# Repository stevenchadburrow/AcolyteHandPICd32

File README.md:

<b><h1>Acolyte Hand PIC'd 32 Retraux Computer and Video Game Console</h1></b>

<b>Background</b>

Why build a "computer"?  Why build a "video game console"?  

I had been programming video games for about 20 years before all of this.  It started in high school on Borland Turbo C++ in the computer lab, and then in college on a Ubuntu Linux computer with g++ and OpenGL.  Most of my early attempts are not even worth mentioning though I tried different genres such as FPS and RTS.  After graduate school and getting a job at the local college as a math teacher, I began trying to make a non-violent video game, namely a <a href="https://en.wikipedia.org/wiki/Harvest_Moon_(video_game)">Harvest Moon</a> clone.  It seems that <a href="https://en.wikipedia.org/wiki/Stardew_Valley">Stardew Valley</a> beat me to it!  After many attempts on many different platforms, including Linux/OpenGL/C++, HTML/Javascript, and Android/Java, I have declared them all as 'demos', though I learned a lot from that time.  Meanwhile, I began programming 'arcade' video games for our annual Math Appreciation Day events, to have on display and allow students to play during the event.  A few are listed <a href="https://github.com/stevenchadburrow/MathDayGames">here</a>.  

In Fall 2021, after starting research on a water-based calculator, I thought to myself, "Wouldn't electricity be so much easier?"  After stumbling upon <a href="https://wilsonminesco.com/">Garth Wilson's 6502 Primer</a>, I emailed him and he invited me to join the <a href="http://forum.6502.org/">6502.org Forum</a>.  I began researching and prototyping (aka breadboarding) with basic logic chips, and learning how to create schematics.  While learning more about digital electronics, I found The 8-Bit Guy, Adrian's Digital Basement, and Ben Eater on Youtube.

Inspired by The 8-Bit Guy's <a href="https://www.youtube.com/watch?v=ayh0qebfD2g">"Dream Computer"</a>, and after many initial attempts (aka failures) and a couple of awesome successes, I eventually produced the original <a href="https://github.com/stevenchadburrow/AcolyteComputer">Acolyte Computer</a> using a W65C02 processor.  I had great help from Garth Wilson and the guys on the 6502.org Forum as I worked through many prototypes to get to that point.  I was able to display this and other projects at the Math Appreciation Day events playing video games such as Space Invaders, Tetris, and Rogue.

From there, the project grew to the <a href="https://github.com/stevenchadburrow/NewAcolyte">New Acolyte</a> coupled with an XC9572XL CPLD, then the <a href="https://github.com/stevenchadburrow/Acolyte816">Acolyte '816</a> using a W65C816 processor coupled with a PIC16F886 microcontroller as a bootloader.  Wanting to continue pursuing PIC microcontrollers, I created the original <a href="https://github.com/stevenchadburrow/AcolyteHandPICd">Acolyte Hand PIC'd</a> using the PIC18F47J13 microcontroller, then the <a href="https://github.com/stevenchadburrow/AcolyteHandPICd24">Acolyte Hand PIC'd 24</a> using the PIC24EP512GP204 microcontroller finally without a coupled CPLD.  During Summer 2024, I programmed a 2-player <a href="https://www.youtube.com/watch?v=8EHRpKk9gPc">Pokemon demo</a> using <a href="https://tuxemon.org/">Tuxemon</a> art assets, pushing that PIC24 to the limit.

This project, the Acolyte Hand PIC'd 32, is supposed to show the culmination of my knowledge in PCB design and microcontroller programming over the past 3 years.  The intention is to create a standardized development platform for many new video games that will be displayed during the Math Appreciation Day events.

<b>Microcontroller</b>

PIC32MZ2048EFH144 running at 200 MHz
<br>
Internal memory of 512KB of RAM and 2MB of Flash ROM

<b>Video</b>

VGA 800x600 max resolution (720x512 typical resolution) at 72 Hz with 256 colors or 65K colors

<b>Audio</b>

Dual 8-bit audio channels

<b>HID</b>

2x Sega Genesis controller ports
<br>
Dual PS/2 port for keyboard and mouse through splitter
<br>
USB port for keyboard, mouse, or Xbox-360 controller

<b>File System</b>

Elm-Chan's <a href="http://elm-chan.org/fsw/ff/">FatFS Generic FAT Filesystem Module</a> using SPI Micro SD Card adapter
<br>
(use command 'sudo mkfs.vfat /dev/sdX' to format SDcard)

<b>UART</b>

FT232RL USB-to-UART adapter
<br>
(use command 'sudo picocom /dev/ttyUSB0' for default 9600 baud connection)

<b>Custom Applications</b>

Tetra - Tetris clone recopied from my previous PIC-related projects
<br>
Scratchpad - Proof-of-concept 'text editor' without save/load features
<br>
AV Demo - Audio/Video playback of modified video files with a resolution 240x192 at 15 FPS with 65K colors and dual 8-bit audio

<b>Gameboy Emulator</b>

Mahyar Koshkouei's <a href="https://github.com/deltabeard/Peanut-GB">Peanut-GB (with MiniGB-APU) Gameboy Emulator</a>
<br>
Added support for GBC default color palettes, custom palettes, game file save/load, and screen size and refresh rate adjustments
<br>
Tested with many games, including: Tetris, Dr. Mario, Balloon Kid, Zelda: Link's Awakening, Tobu Tobu Girl, Pokemon Red, and Pokemon Kanto Expansion Pak

<b>Links</b>

<a href="https://www.aidanmocke.com/">https://www.aidanmocke.com/</a> for a bunch of PIC32MZ projects (without Harmony), including USB.<br>
<a href="http://elm-chan.org/">http://elm-chan.org/</a> for a bunch of projects, including MMC (aka SDcard) and FatFs.<br>
<a href="https://github.com/deltabeard/">https://github.com/deltabeard/</a> for a bunch of projects, including Peanut-GB and MiniGB-APU projects.<br>
<a href="https://hackaday.com/2025/01/13/homebrew-retro-console-runs-on-pic32/">https://hackaday.com/2025/01/13/homebrew-retro-console-runs-on-pic32/</a> for the Hack-A-Day article!<br>

<b>Look Ma, no bodges! (showing Version 2 board)</b>
<br>

<b>3D printed case fits perfectly! (showing Version 1 board)</b>
<br>

<b>Main menu format with splash screen.</b>
<br>

<b>Gotta love some 2-player Tetris!</b>
<br>

<b>It can now play any Gameboy game!</b>
<br>

<b>Audio/Video playback running at 65K colors and dual 8-bit audio.</b>
<br>
&nbsp;&nbsp;&nbsp;&nbsp;&nbsp;&nbsp;&nbsp;&nbsp;

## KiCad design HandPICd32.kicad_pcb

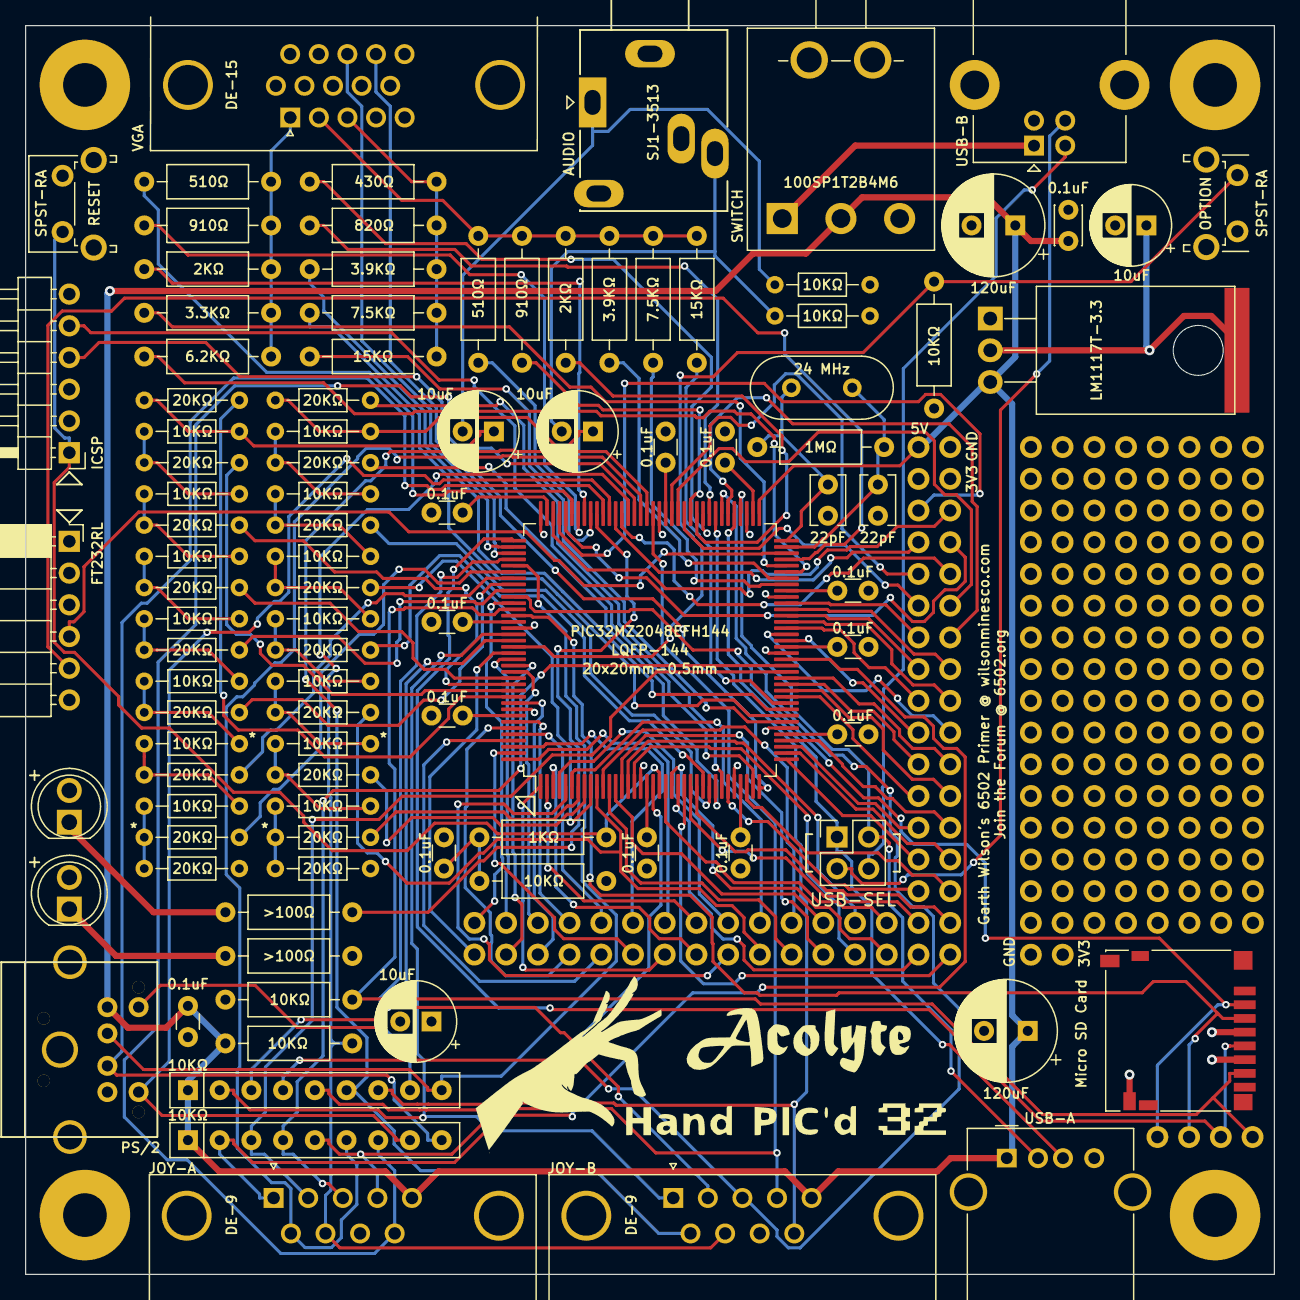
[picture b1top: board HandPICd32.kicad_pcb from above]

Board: 4 copper layers, 100.0 x 100.0 mm, 305 parts (1 on the bottom side), 153 nets.

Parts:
C1, C2, C3, C4, C5, C6, C7, C8, C9, C10, C11, C19: C_Small; C_Disc_D3.0mm_W1.6mm_P2.50mm
C12, C13: C; C_Disc_D3.8mm_W2.6mm_P2.50mm
C14, C20: C_Polarized_Small_US; CP_Radial_D8.0mm_P3.50mm
C16, C22, C23, C24: C_Polarized_Small_US; CP_Radial_D6.3mm_P2.50mm
C21: C_Small; C_Disc_D3.0mm_W2.0mm_P2.50mm
D1, D2: LED; CustomLED
G100: LOGO; HandPinching
G101: LOGO; AcolyteTitle
G102: LOGO; HandPickedTitle
G103: LOGO; PublicPixel32
G104: LOGO; Mystery
J1: Mini-DIN-6; PS2_Din6
J2, J7: DE9_Plug; DSUB-9_Male_Horizontal_P2.77x2.84mm_EdgePinOffset7.70mm_Hou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
J4: DE15_Receptacle_HighDensity; DSUB-15-HD_Female_Horizontal_P2.29x2.54mm_VGA
J5: USB_B; USB_B_Lumberg_2411_02_Horizontal
J6: USB_A; USB_A_Molex_67643_Horizontal
J8: AudioJack3; BIGJack_3.5mm_Ledino_KB3SPRS_Horizontal
J9: Conn_01x06; PinHeader_1x06_P2.54mm_Horizontal
J11: Micro_SD_Card; microSD_HC_Hirose_DM3D-SF
J12: Conn_01x06; PinSocket_1x06_P2.54mm_Horizontal
J14: Conn_02x02_Odd_Even; PinHeader_2x02_P2.54mm_Vertical
R1, R2, R3, R4, R5, R6, R7, R8, R9, R10, R11, R16, R17, R18, R19, R22, R51, R52, R53, R54, R55, R56, R57, R58: R_US; R_Axial_DIN0207_L6.3mm_D2.5mm_P10.16mm_Horizontal
R12, R13, R14, R15, R20, R21, R23, R24, R25, R26, R27, R28, R29, R30, R31, R32, R33, R34, R35, R36, R37, R38, R39, R40, R41, R42, R43, R44, R45, R46, R47, R48, R49, R50: R_US; R_Axial_DIN0204_L3.6mm_D1.6mm_P7.62mm_Horizontal
RN1, RN2: R_Network08_US; R_Array_SIP9
SW1: SW_SPDT; SPDT-100SP1T2B4M6QE
SW2, SW3: SW_Push; SW_Tactile_SPST_Angled_PTS645Vx83-2LFS
TP1, TP2, TP3, TP4, TP5, TP6, TP7, TP8, TP9, TP10, TP11, TP12, TP13, TP14, TP15, TP16, TP17, TP18, TP19, TP20, TP21, TP22, TP23, TP24, TP25, TP26, TP28, TP30, TP36, TP37, TP38, TP39, TP40, TP44, TP45, TP46, TP47, TP50, TP51, TP52, TP53, TP54, TP55, TP58, TP65, TP72, TP73, TP74, TP80, TP81, TP89, TP90, TP91, TP103, TP105, TP106, TP107, TP108, TP115, TP117, TP118, TP119, TP120, TP122, TP123, TP124, TP132, TP137, TP150, TP152, TP154, TP155, TP156, TP157, TP158, TP159, TP160, TP161, TP162, TP163, TP164, TP165, TP166, TP167, TP168, TP169, TP170, TP171, TP172, TP173, TP174, TP175, TP176, TP177, TP178, TP179, TP180, TP181, TP182, TP183, TP184, TP185, TP186, TP187, TP188, TP189, TP190, TP191, TP192, TP193, TP194, TP195, TP196, TP197, TP198, TP199, TP200, TP201, TP202, TP203, TP204, TP205, TP206, TP207, TP208, TP209, TP210, TP211, TP212, TP213, TP214, TP215, TP216, TP217, TP218, TP219, TP220, TP221, TP222, TP223, TP224, TP225, TP226, TP227, TP228, TP229, TP230, TP231, TP232, TP233, TP234, TP235, TP236, TP237, TP238, TP239, TP240, TP241, TP242, TP243, TP244, TP245, TP246, TP247, TP248, TP249, TP250, TP251, TP252, TP253, TP254, TP255, TP256, TP257, TP258, TP259, TP260, TP261, TP262, TP263, TP264, TP265, TP266, TP267, TP268, TP269, TP270, TP271, TP272, TP273, TP274, TP275, TP276, TP277, TP278, TP279: TestPoint; TestPointStdTHT
TP133, TP134, TP135, TP136: TestPoint; ScrewHole-4-40
U1: PIC32MZ2048EFH144-I/PH; LQFP-144_20x20mm_P0.5mm-CUSTOM
U4: LM1117T-3.3; TO-220-3_Horizontal_TabDown-custom
Y1: Crystal; Crystal_HC49-4H_Vertical

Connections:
+3V3: C1.2, C2.2, C3.2, C4.2, C5.2, C6.2, C7.2, C8.2, C9.2, C10.2, C22.1, C23.1, D1.2 (A), D2.2 (A), J9.2, J11.4 (VDD), R2.2, R18.2, R22.2, TP25.1, TP58.1, U1.18 (VDD), U1.33 (VDD), U1.41 (AVDD), U1.55 (VDD), U1.64 (VDD), U1.74 (VUSB3V3), U1.88 (VDD), U1.107 (VDD), U1.122 (VDD), U1.137 (VDD), U4.2 (VO)
+5V: C14.1, C19.2, C20.1, C21.2, J1.4, J2.5, J6.1 (VBUS), J7.5, R16.2, RN1.1 (common), RN2.1 (common), SW1.2 (B), TP7.1, U1.73 (VBUS), U4.3 (VI)
/Pin1: TP1.1, U1.1 (AN23/RG15)
/Pin2: TP2.1, U1.2 (EBIA5/AN34/PMA5/RA5)
/Pin3: TP3.1, U1.3 (EBID5/AN17/RPE5/PMD5/RE5)
/Pin4: TP4.1, U1.4 (EBID6/AN16/PMD6/RE6)
/Pin5: TP5.1, U1.5 (EBID7/AN15/PMD7/RE7)
/Pin6: TP6.1, U1.6 (EBIA6/AN22/RPC1/PMA6/RC1)
/Pin11: TP11.1, U1.11 (EBIA12/AN21/RPC2/PMA12/RC2)
/Pin12: TP12.1, U1.12 (*EBIWE/AN20/RPC3/PMWR/RC3)
/Pin13: TP13.1, U1.13 (*EBIOE/AN19/RPC4/PMRD/RC4)
/Pin14: TP14.1, U1.14 (AN14/C1IND/RPG6/SCK2/RG6)
/Pin15: TP15.1, U1.15 (AN13/C1INC/RPG7/SDA4/RG7)
/Pin16: TP16.1, U1.16 (AN12/C2IND/RPG8/SCL4/RG8)
/Pin21: TP17.1, U1.21 (EBIA2/AN11/C2INC/RPG9/PMA2/RG9)
/Pin22: TP18.1, U1.22 (TMS/AN24/RA0)
/Pin23: TP19.1, U1.23 (AN25/RPE8/RE8)
/Pin24: TP20.1, U1.24 (AN26/RPE9/RE9)
/Pin25: TP21.1, U1.25 (AN45/C1INA/RPB5/RB5)
/Pin26: TP22.1, U1.26 (AN4/C1INB/RB4)
/Pin31: TP28.1, U1.31 (AN3/C2INA/RPB3/RB3)
/Pin34: TP30.1, U1.34 (AN2/C2INB/RPB2/RB2)
/Pin37: TP39.1, U1.37 (PGEC2/AN46/RPB6/RB6)
/Pin38: TP38.1, U1.38 (PGED2/AN47/RPB7/RB7)
/Pin39: TP37.1, U1.39 (VREF-/CVREF-/AN27/RA9)
/Pin40: TP36.1, U1.40 (VREF+/CVREF+/AN28/RA10)
/Pin47: TP47.1, U1.47 (EBIA10/AN48/RPB8/PMA10/RB8)
/Pin48: TP46.1, U1.48 (EBIA7/AN49/RPB9/PMA7/RB9)
/Pin49: TP45.1, U1.49 (CVREFOUT/AN5/RPB10/RB10)
/Pin50: TP44.1, U1.50 (AN6/RB11)
/Pin56: TP40.1, U1.56 (TCK/AN29/RA1)
/Pin57: TP55.1, U1.57 (TDI/AN30/RPF13/SCK5/RF13)
/Pin58: TP54.1, U1.58 (TDO/AN31/RPF12/RF12)
/Pin59: TP53.1, U1.59 (AN7/RB12)
/Pin60: TP52.1, U1.60 (AN8/RB13)
/Pin61: TP51.1, U1.61 (AN9/RPB14/SCK3/RB14)
/Pin62: TP50.1, U1.62 (AN10/RPB15/OCFB/RB15)
/Pin85: TP72.1, U1.85 (SCL2/RA2)
/Pin86: TP73.1, U1.86 (EBIRDY1/SDA2/RA3)
/Pin87: TP74.1, U1.87 (EBIA14/PMCS1/PMA14/RA4)
/Pin95: TP80.1, U1.95 (RPA14/SCL1/RA14)
/Pin96: TP81.1, U1.96 (RPA15/SDA1/RA15)
/Pin105: TP90.1, U1.105 (SOSCI/RPC13/RC13)
/Pin106: TP91.1, U1.106 (SOSCO/RPC14/T1CK/RC14)
/Pin127: TP108.1, U1.127 (EBID9/RPG1/PMD9/RG1)
/Pin128: TP107.1, U1.128 (EBID8/RPG0/PMD8/RG0)
/Pin129: TP106.1, U1.129 (TRCLK/SQICLK/RA6)
/Pin130: TP105.1, U1.130 (TRD3/SQID3/RA7)
/Pin135: TP115.1, U1.135 (EBID0/PMD0/RE0)
/Pin138: TP120.1, U1.138 (EBID1/PMD1/RE1)
/Pin139: TP119.1, U1.139 (TRD2/SQID2/RG14)
/Pin140: TP118.1, U1.140 (TRD1/SQID1/RG12)
/Pin141: TP117.1, U1.141 (TRD0/SQID0/RG13)
/Pin142: TP124.1, U1.142 (EBID2/PMD2/RE2)
/Pin143: TP123.1, U1.143 (EBID3/RPE3/PMD3/RE3)
/Pin144: TP122.1, U1.144 (EBID4/AN18/PMD4/RE4)
AUDIO-OUT-LEFT: C24.2, J8.T, R37.1
AUDIO-OUT-RIGHT: C16.2, J8.R, R50.1
BLUE: J4.3, R3.1, R4.1, R51.1, R52.1, R58.1
GND: C1.1, C2.1, C3.1, C4.1, C5.1, C6.1, C7.1, C8.1, C9.1, C10.1, C11.1, C12.2, C13.2, C14.2, C19.1, C20.2, C21.1, C22.2, C23.2, J1.3, J2.8, J4.5, J4.6, J4.7, J4.8, J4.10, J5.4 (GND), J5.5 (Shield), J6.4 (GND), J6.5 (Shield), J7.8, J8.S, J9.3, J11.6 (VSS), J11.9 (SHIELD), J12.1, R12.2, R17.2, R36.2, R37.2, R50.2, SW2.2, SW3.2, TP26.1, TP132.1, TP133.1, TP134.1, TP135.1, TP136.1, TP137.1, U1.17 (VSS), U1.32 (VSS), U1.42 (AVSS), U1.54 (VSS), U1.63 (VSS), U1.75 (VSS), U1.89 (VSS), U1.108 (VSS), U1.123 (VSS), U1.136 (VSS), U4.1 (GND)
GREEN: J4.2, R5.1, R6.1, R7.1, R53.1, R54.1, R55.1
MCLR-PU: C11.2, R1.1, R22.1
unnamed: C16.1, R48.1, R49.2
unnamed: C24.1, R34.1, R35.2
unnamed: D1.1 (K), R17.1
unnamed: D2.1 (K), R19.1
unnamed: R12.1, R13.2, R14.2
unnamed: R14.1, R15.2, R38.2
unnamed: R20.2, R21.2, R36.1
unnamed: R21.1, R23.2, R24.2
unnamed: R24.1, R25.2, R26.2
unnamed: R26.1, R27.2, R28.2
unnamed: R28.1, R29.2, R30.2
unnamed: R30.1, R31.2, R32.2
unnamed: R32.1, R33.2, R34.2
unnamed: R38.1, R39.2, R40.2
unnamed: R40.1, R41.2, R42.2
unnamed: R42.1, R43.2, R44.2
unnamed: R44.1, R45.2, R46.2
unnamed: R46.1, R47.2, R48.2
Pin7: R13.1, U1.7 (AN35/ETXD0/RJ8)
Pin8: R15.1, U1.8 (AN36/ETXD1/RJ9)
Pin9: R43.1, U1.9 (*EBIBS0/RJ12)
Pin10: R39.1, TP10.1, U1.10 (*EBIBS1/RJ10)
Pin19: J2.1, RN2.2 (R1), U1.19 (EBIA16/RK0)
Pin20: J9.1, R1.2, SW2.1, U1.20 (*MCLR)
Pin27: R41.1, U1.27 (AN37/ERXCLK/EREFCLK/RJ11)
Pin28: R45.1, U1.28 (EBIA13/PMA13/RJ13)
Pin29: R47.1, U1.29 (EBIA11/PMA11/RJ14)
Pin30: R49.1, U1.30 (EBIA0/PMA0/RJ15)
Pin35: J9.5, U1.35 (PGEC1/AN1/RPB1/RB1)
Pin36: J9.4, U1.36 (PGED1/AN0/RPB0/RB0)
Pin43: R58.2, U1.43 (AN38/ETXD2/RH0)
Pin44: R51.2, U1.44 (AN39/ETXD3/RH1)
Pin45: R52.2, U1.45 (*EBIRP/RH2)
Pin46: R53.2, U1.46 (RH3)
Pin51: J2.2, RN2.3 (R2), U1.51 (EBIA1/PMA1/RK1)
Pin52: J2.3, RN2.4 (R3), U1.52 (EBIA3/PMA3/RK2)
Pin53: J2.4, RN2.5 (R4), U1.53 (EBIA17/RK3)
Pin65: R54.2, U1.65 (AN40/ERXERR/RH4)
Pin66: R55.2, U1.66 (AN41/ERXD1/RH5)
Pin67: R56.2, U1.67 (AN42/ERXD2/RH6)
Pin68: R57.2, U1.68 (EBIA4/PMA4/RH7)
Pin69: J12.5, U1.69 (AN32/RPD14/RD14)
Pin70: J12.4, U1.70 (AN33/RPD15/SCK6/RD15)
Pin71: C12.1, R11.1, U1.71 (OSC1/CLKI/RC12), Y1.1
Pin72: C13.1, R11.2, U1.72 (OSC2/CLKO/RC15), Y1.2
Pin76: J6.2 (D-), J14.2, U1.76 (D-)
Pin77: J6.3 (D+), J14.1, U1.77 (D+)
Pin78: TP65.1, U1.78 (RPF3/USBID/RF3)
Pin79: J7.3, RN1.4 (R3), U1.79 (SDA3/RPF2/RF2)
Pin80: J7.9, RN1.7 (R6), U1.80 (SCL3/RPF8/RF8)
Pin81: R3.2, U1.81 (ERXD0/RH8)
Pin82: R4.2, U1.82 (ERXD3/RH9)
Pin83: R5.2, U1.83 (ECOL/RH10)
Pin84: R6.2, U1.84 (EBIRDY2/RH11)
Pin90: J7.4, RN1.5 (R4), U1.90 (EBIA9/RPF4/SDA5/PMA9/RF4)
Pin91: J7.6, RN1.6 (R5), U1.91 (EBIA8/RPF5/SCL5/PMA8/RF5)
Pin92: J2.6, RN2.6 (R5), U1.92 (EBIA18/RK4)
Pin93: J2.9, RN2.7 (R6), U1.93 (EBIA19/RK5)
Pin94: J2.7, J7.7, R16.1, U1.94 (EBIA20/RK6)
Pin97: J1.5, RN2.8 (R7), U1.97 (EBIA15/RPD9/PMCS2/PMA15/RD9)
Pin98: J1.1, RN2.9 (R8), U1.98 (RPD10/SCK4/RD10)
Pin99: R19.2, U1.99 (EMDC/RPD11/RD11)
Pin100: R7.2, U1.100 (ECRS/RH12)
Pin101: R8.2, U1.101 (ERXDV/ECRSDV/RH13)
Pin102: R9.2, U1.102 (RH14)
Pin103: R10.2, U1.103 (EBIA23/RH15)
Pin104: TP89.1, U1.104 (RPD0/RTCC/INT0/RD0)
Pin109: J11.5 (CLK), TP9.1, U1.109 (RPD1/SCK1/RD1)
Pin110: J4.13, U1.110 (EBID14/RPD2/PMD14/RD2)
Pin111: J4.14, U1.111 (EBID15/RPD3/PMD15/RD3)
Pin112: J1.6, RN1.8 (R7), U1.112 (EBID12/RPD12/PMD12/RD12)
Pin113: J1.2, RN1.9 (R8), U1.113 (EBID13/PMD13/RD13)
Pin114: R20.1, U1.114 (ETXERR/RJ0)
Pin115: R23.1, U1.115 (EMDIO/RJ1)
Pin116: R25.1, U1.116 (EBIRDY3/RJ2)
Pin117: R27.1, U1.117 (EBIA22/RJ3)
Pin118: J11.2 (DAT3/CD), TP8.1, U1.118 (*SQICS0/RPD4/RD4)
Pin119: TP103.1, U1.119 (*SQICS1/RPD5/RD5)
Pin120: J11.7 (DAT0), R2.1, TP24.1, U1.120 (ETXEN/RPD6/RD6)
Pin121: J11.3 (CMD), TP23.1, U1.121 (ETXCLK/RPD7/RD7)
Pin124: J7.1, RN1.2 (R1), U1.124 (EBID11/RPF0/PMD11/RF0)
Pin125: J7.2, RN1.3 (R2), U1.125 (EBID10/RPF1/PMD10/RF1)
Pin126: R18.1, SW3.1, U1.126 (EBIA21/RK7)
Pin131: R29.1, U1.131 (*EBICS0/RJ4)
Pin132: R31.1, U1.132 (*EBICS1/RJ5)
Pin133: R33.1, U1.133 (*EBICS2/RJ6)
Pin134: R35.1, U1.134 (*EBICS3/RJ7)
RED: J4.1, R8.1, R9.1, R10.1, R56.1, R57.1
USB-B-D+: J5.3 (D+), J14.3
USB-B-D-: J5.2 (D-), J14.4
USB-POWER: J5.1 (VBUS), SW1.1 (A)

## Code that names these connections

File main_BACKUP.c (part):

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
/*
// Video Color Signals
Pin5,RE7,RED-A
Pin4,RE6,RED-B
Pin3,RE5,RED-C
Pin144,RE4,GREEN-A
Pin143,RE3,GREEN-B
Pin142,RE2,GREEN-C
Pin138,RE1,BLUE-A
Pin135,RE0,BLUE-B

// Video Clock Signals
Pin104,RD0,PIXEL-CLOCK
Pin119,RD5,VISIBLE-CLOCK
Pin110,RD2,H-SYNC
Pin111,RD3,V-SYNC

// Audio
Pin23,RE8,AUDIO-A
Pin24,RE9,AUDIO-B

// SPI SDcard Adapter
Pin120,RD6,MISO
Pin121,RD7,MOSI
Pin109,RD1,SCK1
Pin118,RD4,CS

// PS/2 Keyboard/Mouse
Pin97,RD9,KEY-CLK
Pin98,RD10,KEY-DAT
Pin112,RD12,MOUSE-CLK
Pin113,RD13,MOUSE-DAT

// Joysticks
Pin114,RJ0,JOY-A-UP
Pin115,RJ1,JOY-A-DOWN
Pin116,RJ2,JOY-A-LEFT
Pin117,RJ3,JOY-A-RIGHT
Pin131,RJ4,JOY-A-BUTTON1
Pin132,RJ5,JOY-A-BUTTON2
Pin133,RJ6,JOY-B-UP
Pin134,RJ7,JOY-B-DOWN
Pin10,RJ10,JOY-B-LEFT
Pin9,RJ12,JOY-B-RIGHT
Pin28,RJ13,JOY-B-BUTTON1
Pin29,RJ14,JOY-B-BUTTON2
Pin30,RJ15,JOY-SELECT

// Programmer
Pin20,MCLR
Pin36,RB0,PGED1
Pin35,RB1,PGEC1

// USB0xFF, 0xFF, 0xFF, 0xFF,
Pin77,D+
Pin76,D-Pin29,RJ14,JOY

// Oscillator
Pin71,RC12,OSC1/CLKI
Pin72,RC15,OSC2/CLKO

// UART
Pin69,RD14,U3TX
Pin70,RD15,U3RX

// LED
Pin99,RD11,LED

// Button
Pin27,RJ11,BUTTON
*/


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	
	if (port == 0) // primary port
	{
		PORTDbits.RD9 = 0; // when not floating, ground them
		PORTDbits.RD10 = 0;
		TRISDbits.TRISD9 = 1; // normally they are both floating though
		TRISDbits.TRISD10 = 1; 

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	}
	else if (port == 1) // secondary port (from splitter)
	{
		PORTDbits.RD12 = 0; // when not floating, ground them
		PORTDbits.RD13 = 0;
		TRISDbits.TRISD12 = 1; // normally they are both floating though
		TRISDbits.TRISD13 = 1; 

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	U3MODEbits.ON = 1; // turn UART on
	
	// set up SPI here
	PORTDbits.RD4 = 1; // CS is high
	PORTDbits.RD7 = 1; // MOSI is high
	PORTDbits.RD1 = 0; // CLK is low	
	
	SPI1CONbits.ON = 0; // turn SPI module off
	SPI1CON2 = 0; // disable audio, etc.
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	PORTE = 0;
	
	// turn LED off by default
	PORTDbits.RD11 = 1;
	
	// wait some time
	DelayMS(1000);
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	while (1)
	{
		// blink LED
		PORTDbits.RD11 = 0;
		DelayMS(100);
		DelayMS(100);
		DelayMS(100);
		DelayMS(100);
		DelayMS(100);

		PORTDbits.RD11 = 1;
		DelayMS(100);
		DelayMS(100);
		DelayMS(100);
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			U3TXREG = dummy; // echo character
			
			// blink LED
			//PORTDbits.RD11 = 0;
			//DelayMS(250);
			//PORTDbits.RD11 = 1;
		}
*/
/*
		// blink LED
		PORTDbits.RD11 = 0;
		DelayMS(100);

		PORTDbits.RD11 = 1;
		DelayMS(100);
*/
/*
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			}
		}
		
		PORTDbits.RD11 = 0;
		
		for (unsigned int i=0; i<10000; i++)
		{
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			}
		}
		
		PORTDbits.RD11 = 1;
*/
		//asm("WAIT");

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
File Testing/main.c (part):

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PORTH

// Video Clock Signals
Pin104,RD0,PIXEL-CLOCK
Pin119,RD5,VISIBLE-CLOCK
Pin110,RD2,H-SYNC
Pin111,RD3,V-SYNC

// Audio
PORTJ

// SDcard
Pin120,RD6,MISO
Pin121,RD7,MOSI
Pin109,RD1,SCK1
Pin118,RD4,CS

// PS/2 Keyboard/Mouse
Pin98,RD10,KEY-CLK
Pin99,RD11,KEY-DAT
Pin112,RD12,MOUSE-CLK
Pin113,RD13,MOUSE-DAT

// Joysticks
Pin19,RK0,JOY-A-UP
Pin51,RK1,JOY-A-DOWN
Pin52,RK2,JOY-A-LEFT
Pin53,RK3,JOY-A-RIGHT
Pin92,RK4,JOY-A-BUTTON1
Pin93,RK5,JOY-A-BUTTON2
Pin124,RF0,JOY-B-UP
Pin125,RF1,JOY-B-DOWN
Pin79,RF2,JOY-B-LEFT
Pin90,RF4,JOY-B-RIGHT
Pin91,RF5,JOY-B-BUTTON1
Pin80,RF8,JOY-B-BUTTON2
Pin94,RK6,JOY-SELECT

// Programmer
Pin20,MCLR
Pin36,RB0,PGED1
Pin35,RB1,PGEC1

// USB
Pin78,USBID
Pin77,D+
Pin76,D-

// Oscillator
Pin71,RC12,OSC1/CLKI
Pin72,RC15,OSC2/CLKO

// UART
Pin69,RD14,U3TX
Pin70,RD15,U3RX

// LED
Pin97,RD9,LED

// Button
Pin126,RK7,EXT-BUTTON
*/


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	
	if (port == 0) // primary port
	{
		PORTDbits.RD9 = 0; // when not floating, ground them
		PORTDbits.RD10 = 0;
		TRISDbits.TRISD9 = 1; // normally they are both floating though
		TRISDbits.TRISD10 = 1; 

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	}
	else if (port == 1) // secondary port (from splitter)
	{
		PORTDbits.RD12 = 0; // when not floating, ground them
		PORTDbits.RD13 = 0;
		TRISDbits.TRISD12 = 1; // normally they are both floating though
		TRISDbits.TRISD13 = 1; 

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	while (1)
	{
		// blink LED
		PORTDbits.RD11 = 0;
		DelayMS(100);
		DelayMS(100);
		DelayMS(100);
		DelayMS(100);
		DelayMS(100);

		PORTDbits.RD11 = 1;
		DelayMS(100);
		DelayMS(100);
		DelayMS(100);
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
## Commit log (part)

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2024-12-10 Create LICENSE
2024-12-10 Update LICENSE
2025-02-14 Rename README.MD to README.md
